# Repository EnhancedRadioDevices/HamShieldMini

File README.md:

HamShieldMini1.1 Hardware

You can purchase HamShield Mini (as well as our larger variants or LoRa version) at http://www.enhancedradio.com/

These are the hardware design files for the HamShieldMini1.1 electronics.

These hardware files were created with KiCAD. 
You may need the KiCAD libraries available here: https://github.com/mogar/KiCAD_libs
When opening these projects in KiCAD, you may need to change the path to the libraries from the above link.
This can be done in preferences->libraries in both the schematic editor and the layout editor.
Make sure the libraries noted there point to wherever you put the above KiCAD_libs repo.

# Arduino Connections

To use the HamShieldMini with an Arduino, you can use our standard HamShield library: 

https://github.com/EnhancedRadioDevices/HamShield

The pinout should be:

    1	- SPKR - Arduino Pin A2
    2	- MIC  - Arduino Pin D3
    3	- CLK/SCLK  - Arduino Pin A5
    4	- DAT/SDIO  - Arduino Pin A4
    5	- nCS/nSEN  - Arduino Pin A1
    6	- GND  - Arduino Pin GND
    7	- VCC  - Arduino Pin 5V

# Raspberry Pi Connections

To use the HamShieldMini with a Raspberry Pi, you can use our HamShieldPy library: 

https://github.com/EnhancedRadioDevices/HamShieldPy

The pinout should be:

    2	- MIC  - RPi Pin 12 (wiringPi1, PWM0)
    3	- CLK  - RPi Pin 15 (wiringPi3)
    4	- nCS  - RPi Pin 11 (wiringPi0)
    5	- DAT  - RPi Pin 13 (wiringPi2)
    6	- GND  - RPi Pin 6 (GND)
    7	- VCC  - RPi Pin 1 (3.3V)

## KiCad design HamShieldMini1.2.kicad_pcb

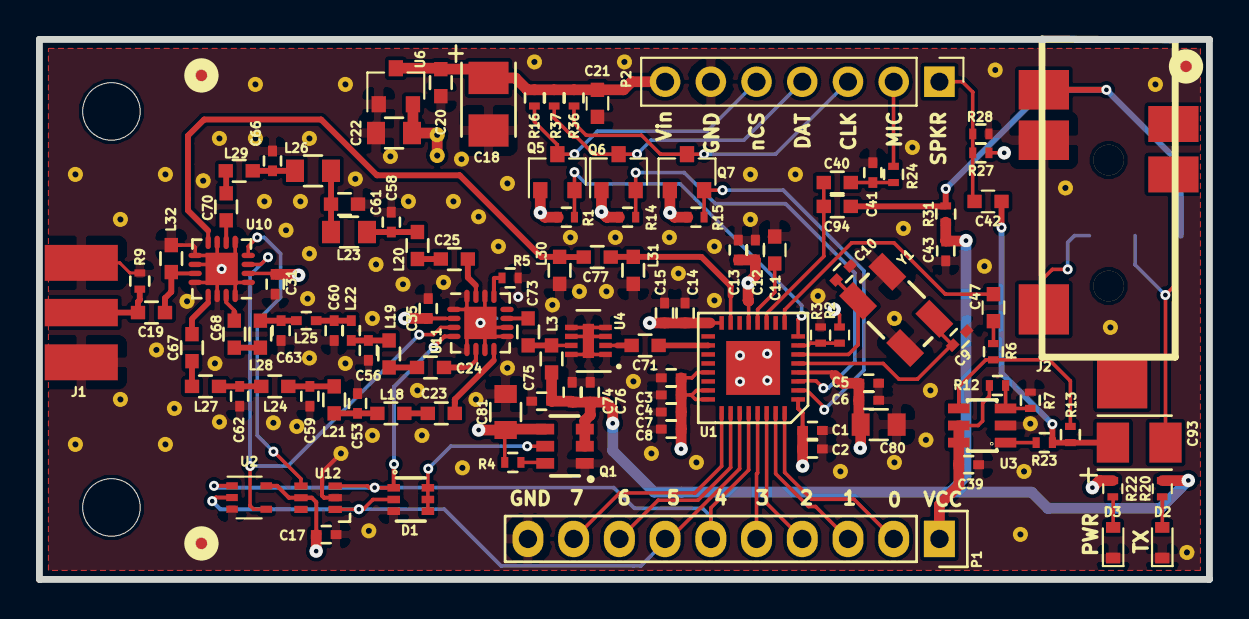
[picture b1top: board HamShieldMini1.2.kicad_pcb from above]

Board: 4 copper layers, 65.0 x 30.0 mm, 118 parts (1 on the bottom side), 71 nets.

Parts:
C1, C3, C5, C7, C12, C14: 1n; C_0402
C2, C4, C6, C8, C17, C31, C35, C39, C43, C75, C76: 0u1; C_0402
C9, C10, C15: 10p; C_0402
C11, C21, C40, C42, C47, C94: 2u2; C_0603
C13: 1u; C_0402
C18, C93: 47u; C1210P
C19, C23, C24, C25, C67, C68, C70, C71, C73, C77: 100p; C_0603
C20: 4.7u; C_0603
C22, C80: 10u; C_0805
C41: 15n; C_0402
C53, C62: 7p; C_0402
C56, C63: 14p; C_0402
C58, C66: 20p; C_0402
C59: 8.2p; C_0402
C60: 15p; C_0402
C61: 24p; C_0603
C74: 10n; C_0402
C81: 22u; C_0805
D1: BAS40TW; SOT-363
D2, D3: LED; D_0603
FD1, FD2, FD3: FIDUCIAL1X2.5; SparkFun-FIDUCIAL-1X2.5
J1: SMA_EDGE; SMA-EDGE-HandSolder
J2: SJ-43514-SMT-TR
JP3: M04PTH; PinHeader_SMT_rightAngle_0.1inPitch_4pos
L3: 470n; C_0603
L18, L27: 24n; C_0603
L19, L28: 47n; C_0603
L20, L29: 82n; C_0603
L21, L24: 33n; C_0603
L22, L25: 75n; C_0402
L23, L26: 120n; C_0805
L30, L31, L32: DNP; C_0603
MK1, MK2: MountingHole; MountingHole_3.2mm_M3
P1: Conn_01x10; Pin_Header_Straight_1x10
P2: Conn_01x07; Pin_Header_Straight_1x07_Pitch2.54mm
Q1: NTGD1100L; SC-74
Q5, Q6, Q7: BSS138; SOT-23
R1, R4, R6, R7, R9, R12, R13, R14, R15, R16, R36, R37: 10k; R_0402
R2: 0; R_0402
R3: DNP; R_0402
R5: 49.9; R_0402
R20, R22: 330; R_0402
R23: 13.3; R_0402
R24: 1.47k; R_0402
R27, R28: 100k; R_0402
R31: 2k; R_0402
U1: AU1846; QFN32-5x5
U2: NC7SZ86; SOT-353_SC-70-5
U3: AD8591; SOT23-6
U4: ADL5530; LFCSP-8-1EP_2x3mm_Pitch0.5mm
U6: AP2125N-3.3TRG1; SOT-23
U10, U11: PE42440; QFN-16-1EP_3x3mm_Pitch0.5mm
U12: NC7WZ14; SC-70-6
Y1: 12.8MHz; CRYSTAL-SMD-5X3

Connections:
/AFOUT: C47.2, U1.9
/CLK: Q7.2, R15.2, U1.2
/DAT: Q6.2, R14.2, U1.3
/GPIO0: P1.2, U1.32
/GPIO1: P1.3, U1.31
/GPIO2: P1.4, U1.30
/GPIO3: P1.5, U1.29
/GPIO4: D1.1, P1.6, U1.28, U2.1, U11.4, U12.3
/GPIO5: D1.2, P1.7, U1.27, U2.2, U12.1
/GPIO6: P1.8, U1.26
/GPIO7: P1.9, U1.25
/MIC_IN: C40.2, C94.2, U1.11
/MODE: R2.2, R3.2, U1.7
/RF Front End/1.2m_IN: C24.1, U11.6
/RF Front End/1.2m_OUT: C68.1, U10.15
/RF Front End/2m_IN: C25.2, U11.15
/RF Front End/2m_OUT: C70.2, U10.6
/RF Front End/70cm_IN: C23.1, U11.8
/RF Front End/70cm_OUT: C67.1, U10.13
/RF Front End/ANT: C19.2, L32.1, U10.11
/RF Front End/RF_OUT: C71.1, U1.18
/RF Front End/STAGE1_OUT: C73.2, U11.11
/RF Front End/V1xorV2: U2.4, U10.3, U11.3
/RFin: C77.2, L31.2, U1.15
/User Interface/ARD_AUDIO_OUT: C42.1, P2.1, R27.2, R28.2
/User Interface/PWM_AUDIO_IN: P2.2, R24.1
/Y1: U10.4, U12.4
/nCS: Q5.2, R1.2, U1.8
GND: C1.1, C2.1, C3.1, C4.1, C5.1, C6.1, C7.1, C8.1, C9.1, C10.1, C11.1, C12.1, C13.1, C14.1, C15.1, C17.1, C18.2, C20.2, C21.2, C22.2, C31.2, C35.2, C39.1, C41.1, C43.2, C53.2, C56.2, C58.2, C59.2, C60.2, C61.2, C62.2, C63.2, C66.2, C74.2, C75.2, C76.2, C80.2, C81.2, D1.3, D2.1, D3.1, J1.GND, J2.4, JP3.4, L30.1, L31.1, L32.2, P1.10, P2.6, Q1.1, R3.1, R5.2, R7.2, R9.2, R28.1, U1.33, U2.3, U3.2, U4.1, U4.3, U4.4, U4.5, U4.6, U4.8, U4.9, U6.1, U10.1, U10.5, U10.7, U10.9, U10.10, U10.12, U10.14, U10.16, U10.17, U11.1, U11.5, U11.7, U11.9, U11.10, U11.14, U11.16, U11.17, U12.2, Y1.2, Y1.4
unnamed: C9.2, U1.5, Y1.1
unnamed: C10.2, U1.6, Y1.3
unnamed: C11.2, U1.12
unnamed: C19.1, J1.SIG, R9.1
unnamed: C23.2, L18.1
unnamed: C24.2, L19.1
unnamed: C25.1, L20.1
unnamed: C40.1, C41.2, R24.2
unnamed: C42.2, C93.1, R13.1, R23.1
unnamed: C47.1, R6.2
unnamed: C53.1, L18.2, L21.1
unnamed: C56.1, L19.2, L22.1
unnamed: C58.1, L20.2, L23.1
unnamed: C59.1, L21.2, L24.1
unnamed: C60.1, L22.2, L25.1
unnamed: C61.1, L23.2, L26.1
unnamed: C62.1, L24.2, L27.1
unnamed: C63.1, L25.2, L28.1
unnamed: C66.1, L26.2, L29.1
unnamed: C67.2, L27.2
unnamed: C68.2, L28.2
unnamed: C70.1, L29.2
unnamed: C71.2, U4.2
unnamed: C73.1, L3.2, U4.7
unnamed: C77.1, L30.2, U10.8
unnamed: C93.2, J2.3, JP3.2
unnamed: C94.1, J2.1, JP3.1, R31.1
unnamed: D1.4, D1.5, D1.6, Q1.5
unnamed: D2.2, R20.2
unnamed: D3.2, R22.2
unnamed: J2.2, JP3.3
unnamed: P2.3, Q7.3, R36.2
unnamed: P2.4, Q6.3, R37.2
unnamed: P2.5, Q5.3, R16.2
unnamed: Q1.6, R4.2
unnamed: R5.1, U11.13
unnamed: R7.1, R12.1, U3.3
unnamed: R6.1, R13.2, U3.4
unnamed: R23.2, U3.1
VCC: C1.2, C2.2, C3.2, C4.2, C5.2, C6.2, C7.2, C8.2, C12.2, C13.2, C14.2, C15.2, C17.2, C22.1, C31.1, C35.1, C39.2, C80.1, P1.1, Q5.1, Q6.1, Q7.1, R1.1, R2.1, R12.2, R14.1, R15.1, R22.1, R27.1, U1.1, U1.4, U1.13, U1.16, U1.21, U1.23, U1.24, U2.5, U3.5, U3.6, U6.2, U10.2, U11.2, U12.5
VIN: C18.1, C20.1, C21.1, C81.1, P2.7, Q1.4, R4.1, R16.1, R36.1, R37.1, U6.3
VTX: C43.1, C74.1, C75.1, C76.1, L3.1, Q1.2, Q1.3, R20.1, R31.2

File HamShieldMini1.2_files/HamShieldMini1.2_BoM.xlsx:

Id | Designator | Package | Quantity | Designation | Mfg | Mfg PN | Distributor | Dist PN | Substitution Mfg | Substitution Mfg PN | Substitution Dist PN
1 | U11,U10 | QFN16-3x3mm-0.5mmP | 2 | PE42440MLBB-Z | pSemi | PE42440MLBB-Z | DigiKey | 1046-1038-1-ND
2 | J2 | SJ-43514-SMT-TR | 1 | SJ-43514-SMT-TR | CUI | SJ-43514-SMT-TR | DigiKey | CP-43514SJDKR-ND
3 | U1 | QFN32-5x5 | 1 | AU1846 | Auctus | AU1846 | Auctus | AU1846
4 | U3 | SOT23-6 | 1 | AD8591 | Analog Devices | AD8591ARTZ-REEL7 | DigiKey | AD8591ARTZ-REEL7DKR-ND
5 | P1 | Pin_Header_Straight_1x10 | 1 | CONN_01X10 | DNP | DNP | DNP | DNP
6 | P2 | Pin_Header_Straight_1x7 | 1 | CONN_01X7 | DNP | DNP | DNP | DNP
7 | C20 | C_0603 | 1 | 4.7u | Yageo | CC0603KRX5R6BB475 | DigiKey | 311-1455-2-ND
8 | C1,C3,C5,C7,C12,C14 | C_0402 | 6 | 1n | Yageo | CC0402KRX7R9BB102 | DigiKey | 311-1036-6-ND
9 | C2,C4,C6,C8,C17,C31,C35,C39,C43,C75,C76 | C_0402 | 11 | 0u1 | Taiyo-Yuden | LMK105BJ104KV-F | DigiKey | 587-1227-1-ND
10 | C9,C10,C15 | C_0402 | 3 | 10p | Murata | GJM1555C1H100JB01D | DigiKey | 490-3113-2-ND
11 | C13 | C_0402 | 1 | 1u | Murata | GRM155R61A105KE15J | DigiKey | 490-6298-2-ND
12 | C19,C23,C24,C25,C67,C73,C68,C70,C71,C77 | C_0603 | 10 | 100p | Johanson | 251R14S101JV4T | DigiKey | 712-1310-2-ND
13 | C40,C94,C42,C47,C21,C11 | C_0603 | 6 | 2u2 | Taiyo-Yuden | JMK107BJ225KAHT | DigiKey | 587-3386-6-ND
14 | C41 | C_0402 | 1 | 15n | Samsung | CL05B153KB5VPNC | DigiKey | 1276-6846-6-ND
15 | C56,C63 | C_0402 | 2 | 14p | AVX | 04025U140GAT2A | Mouser | 581-04025U140GAT2A
16 | C59 | C_0402 | 1 | 8.2p | Murata | GJM1555C1H8R2CB01D | DigiKey | 490-3110-2-ND
17 | C60 | C_0402 | 1 | 15p | Murata | GJM1555C1H150JB01D | DigiKey | 490-3117-2-ND
18 | C74 | C_0402 | 1 | 10n | Taiyo-Yuden | UMK105B7103KV-F | DigiKey | 587-2238-2-ND
19 | R2 | R_0402 | 1 | 0 | Vishay Dale | CRCW04020000Z0ED | DigiKey | 541-0.0JDKR-ND
20 | R36,R37,R1,R14,R15,R16,R12,R13,R4,R6,R7,R9 | R_0402 | 12 | 10k | TE Connectivity | 1622826-4 | DigiKey | A106045TR-ND
21 | R23 | R_0402 | 1 | 13.3 | Vishay Dale | CRCW040213R3FKED | DigiKey | 541-13.3LDKR-ND
22 | R24 | R_0402 | 1 | 1.47k | Yageo | RC0402FR-071K47L | DigiKey | YAG3038TR-ND
23 | R27,R28 | R_0402 | 2 | 100k | Vishay Dale | CRCW0402100KJNED | DigiKey | 541-100KJDKR-ND
24 | R31 | R_0402 | 1 | 2k | Vishay Dale | CRCW04022K00JNED | DigiKey | 541-2.0KJDKR-ND
25 | Q1 | SC-74 | 1 | NTGD1100L | ON Semi | NTGD1100L | DigiKey | NTGD1100LT1GOSTR-ND
26 | R5 | R_0402 | 1 | 49.9 | Yageo | RC0402FR-0749R9L | DigiKey | 311-49.9LRTR-ND
27 | D1 | SOT-363 | 1 | BAS40TW | Diodes Inc. | BAS40TW | DigiKey | BAS40TW-FDITR-ND
28 | C58,C66 | C_0402 | 2 | 20p | Murata | GJM1555C1H200JB01D | DigiKey | 490-3120-2-ND
29 | U12 | SC-70-6 | 1 | NC7WZ14 | Fairchild Semi | NC7WZ14 | DigiKey | NC7WZ14P6XTR-ND
30 | C61 | C_0603 | 1 | 24p | Murata | GQM1885C1H240GB01D | DigiKey | 490-8131-2-ND
31 | L18,L27 | C_0603 | 2 | 24n | Murata | LQW18AN24NJ00D | DigiKey | 490-6878-2-ND
32 | L19,L28 | C_0603 | 2 | 47n | Bourns | CW160808-47NJ | DigiKey | CW160808-47NJTR-ND
33 | L21,L24 | C_0603 | 2 | 33n | Murata | LQW18AN33NJ00D | DigiKey | 490-1175-2-ND
34 | C53,C62 | C_0402 | 2 | 7p | Murata | GJM1555C1H7R0CB01D | DigiKey | 490-3107-2-ND
35 | L22,L25 | C_0402 | 2 | 75n | Murata | LQW15AN75NJ00D | DigiKey | 490-6843-1-ND
36 | L23,L26 | C_0805 | 2 | 120n | Bourns | PM0805-R12K-RC | DigiKey | M8464TR-ND
37 | C18,C93 | C1210P | 2 | 47u | AVX | TAJB476K010RNJ | DigiKey | 478-1693-2-ND
38 | U4 | LFCSP-8-1EP_2x3mm_Pitch0.5mm | 1 | ADL5530 | Analog Devices | ADL5530 | DigiKey | ADL5530ACPZ-R7CT-ND
39 | L30,L31,L32 | C_0603 | 3 | DNP
40 | C22,C80 | C_0805 | 2 | 10u | Murata | GRM21BR61E106KA73L | DigiKey | 490-5523-2-ND
41 | L3 | C_0603 | 1 | 470n | Abracon | AISC-0603F-R47J-T | DigiKey | 535-12525-1-ND
42 | L20,L29 | C_0603 | 2 | 82n | Bourns | PM0603-82NJ-RC | DigiKey | M8491TR-ND
43 | C81 | C_0805 | 1 | 22u | Samsung | CL21A226MQQNNNE | DigiKey | 1276-1100-2-ND
44 | J1 | SMA-EDGE-HandSolder | 1 | DNP | Linx | CONSMA003.062 | DigiKey | CONSMA003.062-ND
45 | R3 | R_0402 | 1 | DNP
46 | D2,D3 | D_0603 | 2 | LED | Lite-On | LTST-C190KGKT | DigiKey | 160-1435-2-ND
47 | R20,R22 | R_0402 | 2 | 330 | Yageo | RC0402JR-07330RL | DigiKey | 311-330JRTR-ND
48 | JP3 | PinHeader_SMT_rightAngle_0.1inPitch_4pos | 1 | DNP
49 | Q5,Q6,Q7 | SOT-23 | 3 | BSS138 | Fairchild Semi | BSS138 | DigiKey | BSS138TR-ND
50 | U6 | SOT-23 | 1 | AP2125N-3.3TRG1 | Diodes Inc. | AP2125N-3.3TRG1 | DigiKey | AP2125N-3.3TRG1DITR-ND
51 | Y1 | CRYSTAL-SMD-5X3 | 1 | 12.8MHz | CTS | 405C11A12M80000 | DigiKey | CTX957DKR-ND
52 | U2 | SC70-5 | 1 | NC7SZ86 | ON Semi | NC7SZ86P5X | DigiKey | NC7SZ86P5XCT-ND

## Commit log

2019-01-19 adding gitignore
2019-01-19 adding all files
2019-03-15 unify pin naming scheme
2019-06-20 CLK Pin 3 goes to Arduino A5, not A6
    Probably was a typo, fixed. Bad joo joo for noobs when there's a pin error in README.md :-)
2019-06-20 Fixed nCS and DAT pin numbers
